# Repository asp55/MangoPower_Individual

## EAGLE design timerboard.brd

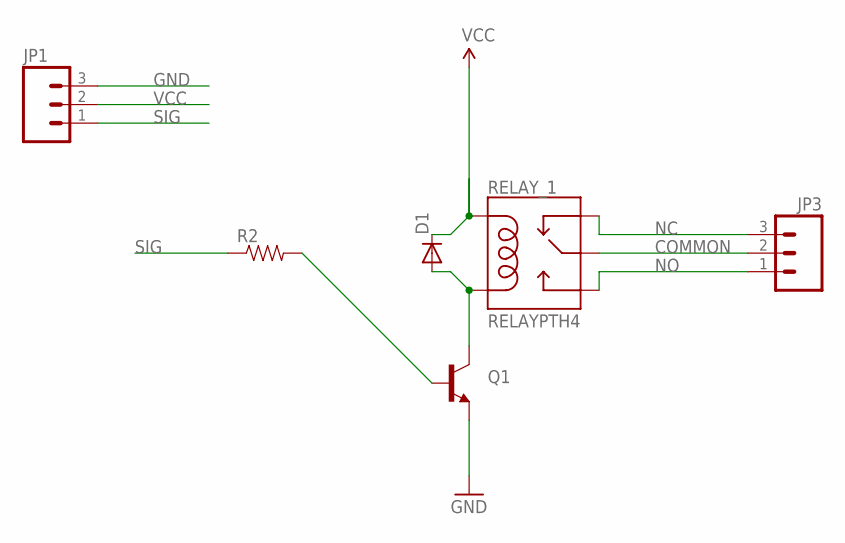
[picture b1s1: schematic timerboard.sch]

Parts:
D1: DIODE1N4148; DIODE-1N4148
JP1: M03PTH; 1X03
JP3: M03-SCREW-5MM; SCREWTERMINAL-5MM-3
Q1: TRANSISTOR_NPNTO-92-AMMO; TO-92-AMMO
R2: RESISTORPTH-1/4W; AXIAL-0.4
RELAY_1: RELAYPTH4; RELAY-JZC

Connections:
COMMON: JP3.2, RELAY_1.4 (MAIN)
GND: JP1.3, Q1.1 (E)
unnamed: D1.A, Q1.3 (C), RELAY_1.1 (COIL2)
unnamed: Q1.2 (B), R2.P$2 (2)
NC: JP3.3, RELAY_1.2 (NC)
NO: JP3.1, RELAY_1.3 (NO)
SIG: JP1.1, R2.P$1 (1)
VCC: D1.C, JP1.2, RELAY_1.5 (COIL1)

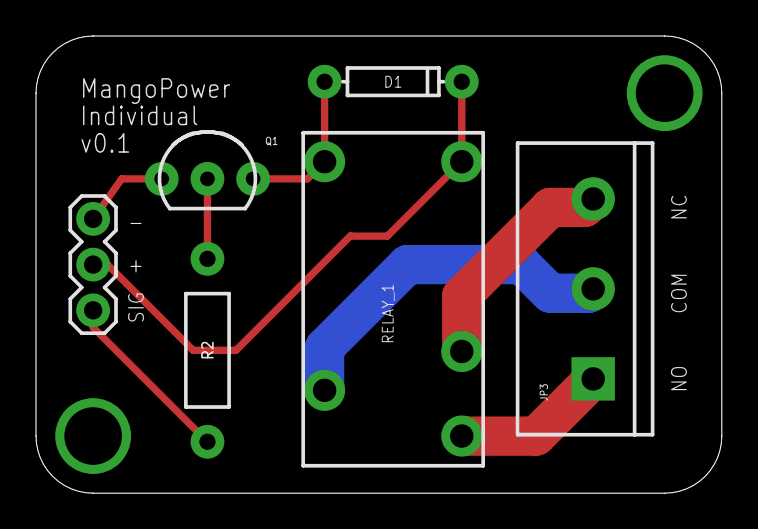
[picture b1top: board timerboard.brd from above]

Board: 2 copper layers, 38.1 x 25.4 mm, 6 parts (0 on the bottom side), 8 nets.

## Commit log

2015-04-16 Created schematic and board, based on MangoPower, but for module use.

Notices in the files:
parts and their libraries:
SparkFun-Connectors: Licensing: Creative Commons ShareAlike 4.0 International - https://creativecommons.org/licenses/by-sa/4.0
